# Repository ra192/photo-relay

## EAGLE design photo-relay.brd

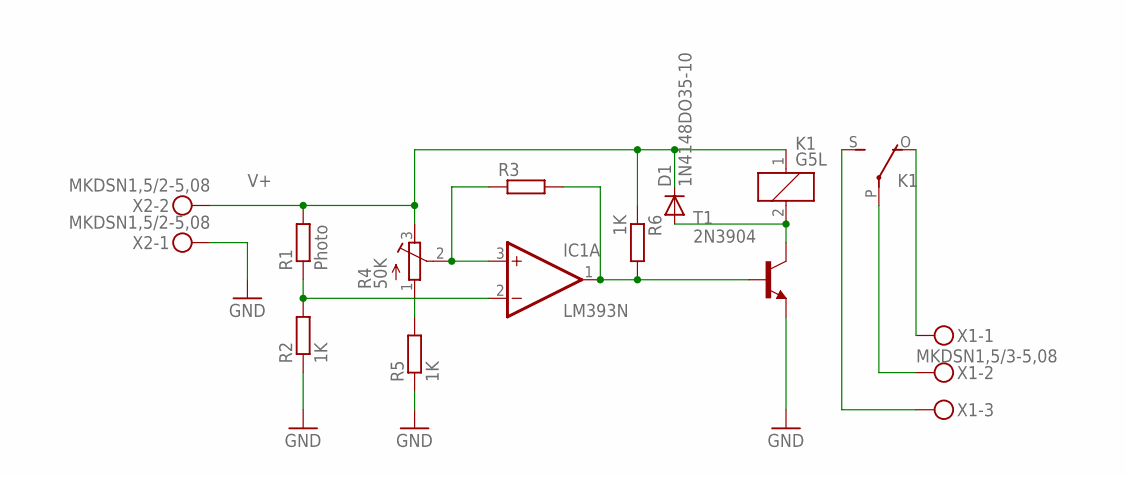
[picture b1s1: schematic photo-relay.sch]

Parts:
D1: 1N4148DO35-10; DO35-10
IC1: LM393N; DIL08
K1: G5L; G5LE
R1: Photo; 0204/7
R2, R5, R6: 1K; 0204/7
R3: R-EU_0204/7; 0204/7
R4: 50K; RTRIM64W
T1: 2N3904; TO92
X1: MKDSN1,5/3-5,08
X2: MKDSN1,5/2-5,08

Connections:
GND: R2.1, R5.1, T1.3 (E), X2.1
unnamed: IC1.1 (OUT), R3.2, R6.2, T1.2 (B)
unnamed: IC1.3 (+IN), R3.1, R4.2 (S)
unnamed: R4.1 (A), R5.2
unnamed: IC1.2 (-IN), R1.1, R2.2
unnamed: K1.P, X1.2
unnamed: D1.A, K1.2, T1.1 (C)
unnamed: K1.S, X1.3
unnamed: K1.O, X1.1
V+: D1.C, IC1.8 (V+), K1.1, R1.2, R4.3 (E), R6.1, X2.2
V-: IC1.4 (V-)

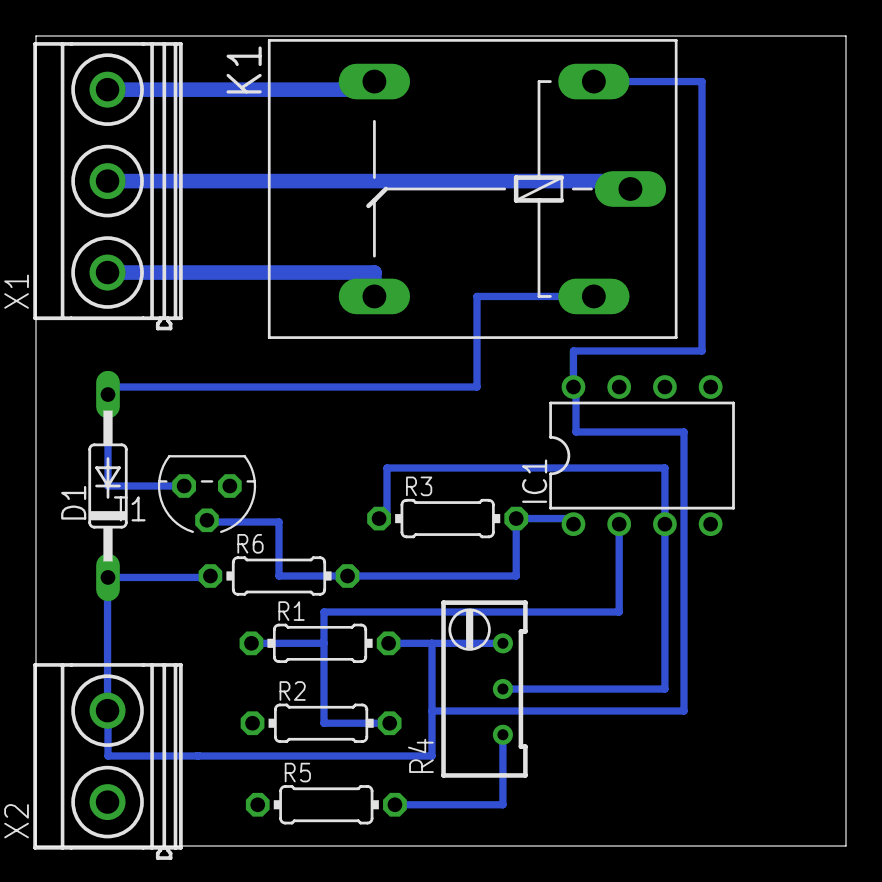
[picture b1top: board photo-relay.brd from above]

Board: 2 copper layers, 45.0 x 45.0 mm, 12 parts (0 on the bottom side), 10 nets.

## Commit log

2016-01-29 minor changes
2016-01-29 add svg
2016-02-02 minor fix
2016-02-02 minor fix.
2016-02-21 fix. transistor connection
2016-02-23 change relay
